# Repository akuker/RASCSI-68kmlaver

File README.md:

# RASCSI-68kmlaver
A scsi emulator based off of the work of http://www.geocities.jp/kugimoto0715/rascsi/index.html

# ATTENTION:
This repository is being archived. The current working version of the board has been moved to:
https://github.com/akuker/RASCSI/tree/master/hw/Dual_Connector_RaSCSI

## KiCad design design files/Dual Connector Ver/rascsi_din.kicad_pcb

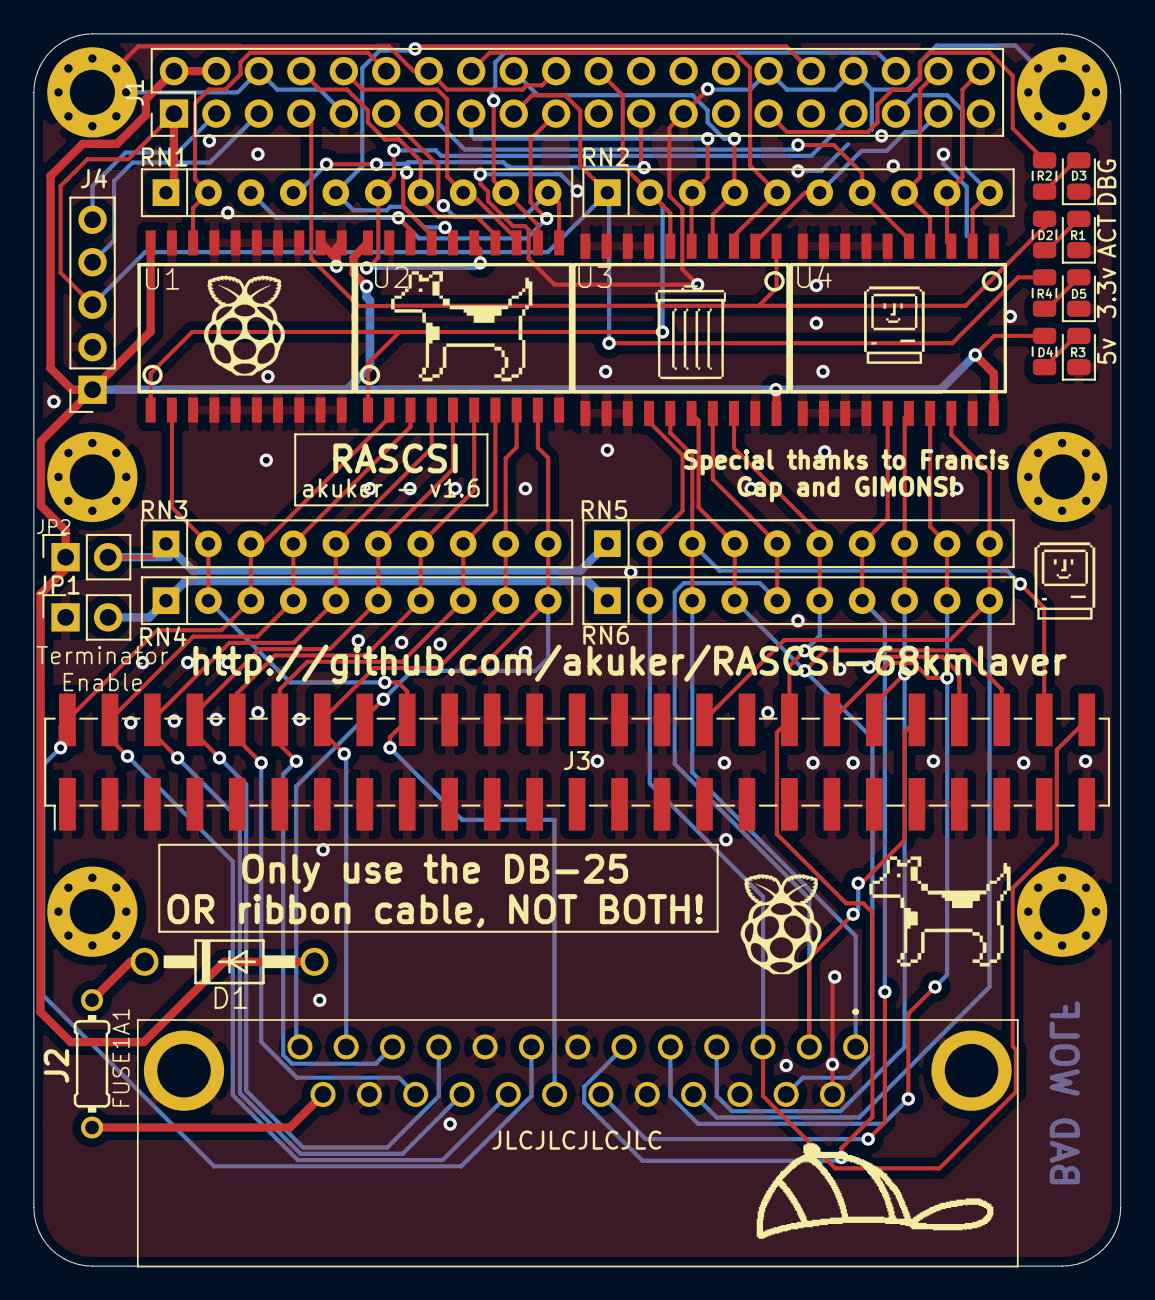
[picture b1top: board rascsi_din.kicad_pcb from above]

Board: 2 copper layers, 65.0 x 73.7 mm, 40 parts (0 on the bottom side), 51 nets.

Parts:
D1: 1N4004; DO41-10
D2, D3, D4, D5: LED_Small; LED_0805_2012Metric
FUSE1A1: R-US_0204_7; 0204_7
H1: Hole1; MountingHole_2.7mm_M2.5_Pad_Via
H2: Hole2; MountingHole_2.7mm_M2.5_Pad_Via
H3: Hole3; MountingHole_2.7mm_M2.5_Pad_Via
H4: Hole5; MountingHole_2.7mm_M2.5_Pad_Via
H5: Hole4; MountingHole_2.7mm_M2.5_Pad_Via
H6: Hole6; MountingHole_2.7mm_M2.5_Pad_Via
J1: Raspberry_Pi_2_3; PinHeader_2x20_P2.54mm_Vertical
J2: DLS3XS6AK44X
J3: Conn_02x25_Odd_Even; PinHeader_2x25_P2.54mm_Vertical_SMD
J4: I2C Pinout; PinSocket_1x05_P2.54mm_Vertical
JP1: Term_Enable_GND; PinSocket_1x02_P2.54mm_Vertical
JP2: Term_Enable_5v; PinSocket_1x02_P2.54mm_Vertical
L1: Mac; mac_happy_small
L2: Dogcow; dogcow
L3: Mac2; mac_happy_small
L4: Dogcow2; dogcow
L5, L7: Raspberry Pi; pi_logo
L6: Mac Trashcan; mac_trashcan
R1, R2, R4: 44; R_0805_2012Metric
R3: 112; R_0805_2012Metric
RN1, RN2: 10k; R_Array_SIP10
RN3, RN5: 220; R_Array_SIP10
RN4, RN6: 330; R_Array_SIP10
U1, U2, U3, U4: SN74LS641-1C; SOIC20S
U$1: LOGO

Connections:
+3V3: J1.1, J1.17, J4.3, R4.1, RN1.1, RN2.1
+5V: D1.A, J1.2, J1.4, J4.1, JP2.1, R3.1, U1.20, U2.20, U3.20, U4.20
C-ACK: J2.5, J3.38, RN5.9, RN6.9, U4.17
C-ATN: J2.17, J3.32, RN5.10, RN6.10, U4.18
C-BSY: J2.6, J3.36, RN5.6, RN6.6, U3.18
C-C_D: J2.15, J3.46, RN5.4, RN6.4, U3.16
C-D0: J2.8, J3.2, RN3.3, RN4.3, U2.2
C-D1: J2.21, J3.4, RN3.4, RN4.4, U2.3
C-D2: J2.22, J3.6, RN3.5, RN4.5, U2.4
C-D3: J2.10, J3.8, RN3.6, RN4.6, U2.5
C-D4: J2.23, J3.10, RN3.7, RN4.7, U2.6
C-D5: J2.11, J3.12, RN3.8, RN4.8, U2.7
C-D6: J2.12, J3.14, RN3.9, RN4.9, U2.8
C-D7: J2.13, J3.16, RN3.10, RN4.10, U2.9
C-DP: J2.20, J3.18, RN3.2, RN4.2, U1.2
C-I_O: J2.3, J3.50, RN5.2, RN6.2, U3.14
C-MSG: J2.2, J3.42, RN5.5, RN6.5, U3.17
C-REQ: J2.1, J3.48, RN5.3, RN6.3, U3.15
C-RST: J2.4, J3.40, RN5.8, RN6.8, U4.16
C-SEL: J2.19, J3.44, RN5.7, RN6.7, U4.15
DBG_LED: J1.29, R2.1
GND: D2.1, D3.1, D4.1, D5.1, H1.1, H2.1, H3.1, H4.1, H5.1, H6.1, J1.6, J1.9, J1.14, J1.20, J1.25, J1.30, J1.34, J1.39, J2.7, J2.9, J2.14, J2.16, J2.18, J2.24, J2.MH1, J2.MH2, J3.1, J3.3, J3.5, J3.7, J3.9, J3.11, J3.13, J3.15, J3.17, J3.19, J3.20, J3.21, J3.22, J3.23, J3.24, J3.27, J3.28, J3.29, J3.30, J3.31, J3.33, J3.35, J3.37, J3.39, J3.41, J3.43, J3.45, J3.47, J3.49, J4.2, JP1.1, U1.3, U1.4, U1.5, U1.6, U1.7, U1.8, U1.9, U1.10, U1.11, U1.12, U1.13, U1.14, U1.15, U1.16, U1.17, U1.19, U2.10, U2.19, U3.7, U3.8, U3.9, U3.10, U3.11, U3.12, U3.13, U3.19, U4.1, U4.6, U4.7, U4.8, U4.9, U4.10, U4.11, U4.12, U4.13, U4.14, U4.19
unnamed: D1.C, FUSE1A1.2
unnamed: D2.2, R1.2
unnamed: D3.2, R2.2
unnamed: D4.2, R3.2
unnamed: D5.2, R4.2
unnamed: JP1.2, RN4.1, RN6.1
unnamed: JP2.2, RN3.1, RN5.1
PI-ACK: J1.40, RN2.9, U4.3
PI-ACT: J1.7, R1.1, U3.1
PI-ATN: J1.35, RN2.10, U4.2
PI-BSY: J1.37, RN2.6, U3.2
PI-C_D: J1.18, RN2.4, U3.4
PI-D0: J1.19, RN1.3, U2.18
PI-D1: J1.23, RN1.4, U2.17
PI-D2: J1.32, RN1.5, U2.16
PI-D3: J1.33, RN1.6, U2.15
PI-D4: J1.8, RN1.7, U2.14
PI-D5: J1.10, RN1.8, U2.13
PI-D6: J1.36, RN1.9, U2.12
PI-D7: J1.11, RN1.10, U2.11
PI-DP: J1.12, RN1.2, U1.18
PI-I_O: J1.22, RN2.2, U1.1, U2.1, U3.6
PI-MSG: J1.16, RN2.5, U3.3
PI-REQ: J1.15, RN2.3, U3.5
PI-RST: J1.38, RN2.8, U4.4
PI-SEL: J1.13, RN2.7, U4.5
PI_SCL: J1.5, J4.4
PI_SDA: J1.3, J4.5
TERMPOW: FUSE1A1.1, J2.25

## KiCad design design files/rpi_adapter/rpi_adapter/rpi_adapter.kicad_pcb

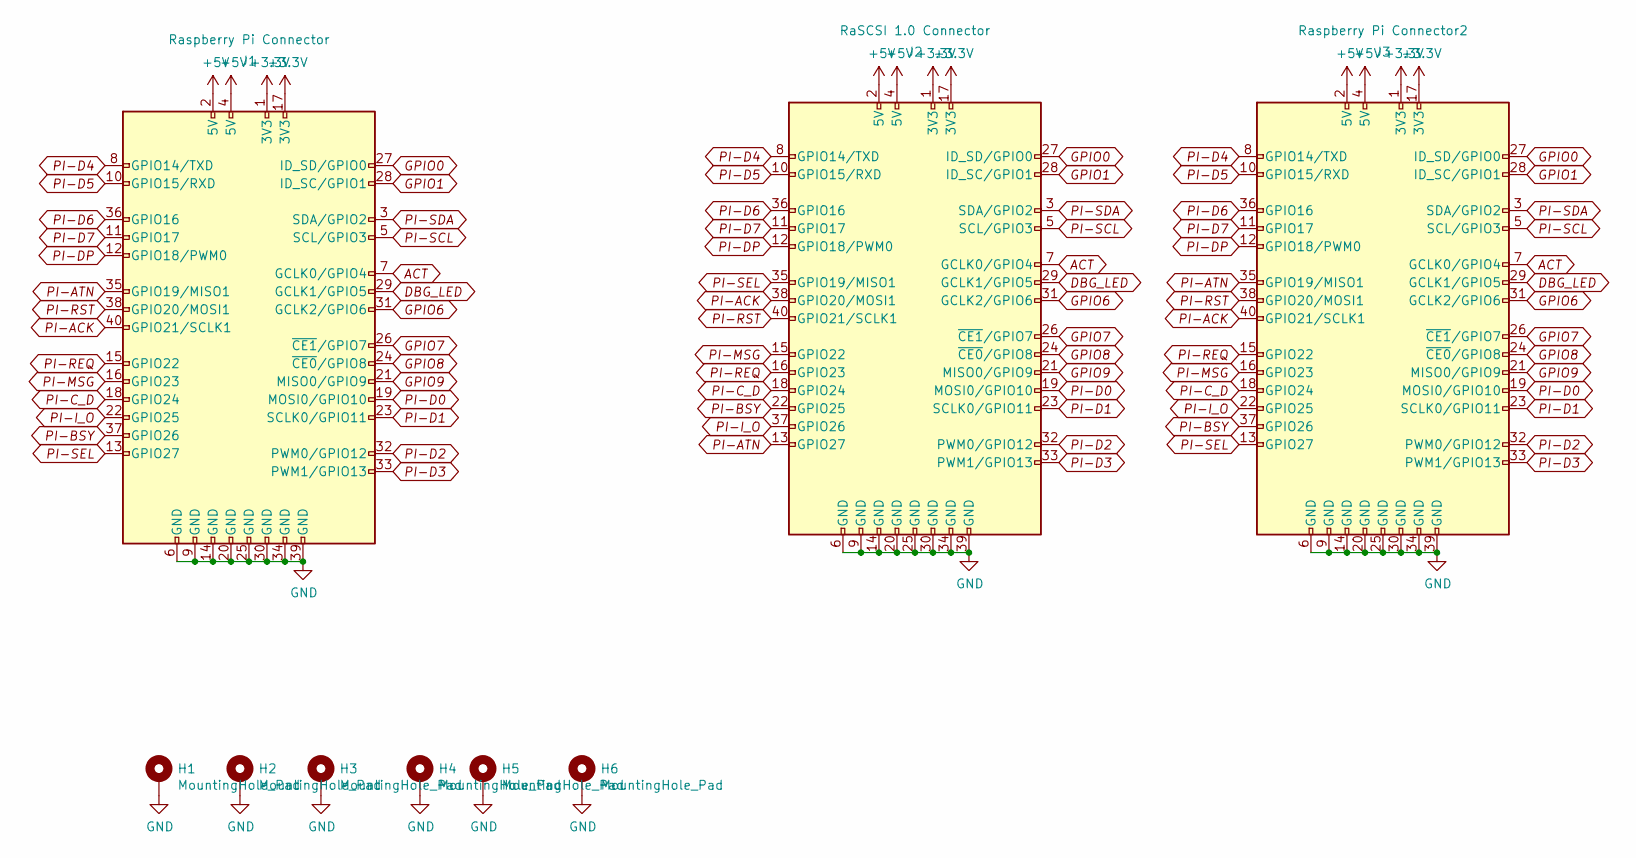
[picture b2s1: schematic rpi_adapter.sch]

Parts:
H1, H2, H3, H4, H5, H6: MountingHole_Pad; MountingHole_2.7mm_M2.5_Pad_Via
J1: Raspberry Pi Connector; PinHeader_2x20_P2.54mm_Vertical
J2: RaSCSI 1.0 Connector; PinHeader_2x20_P2.54mm_Vertical
J3: Raspberry Pi Connector2; PinHeader_2x20_P2.54mm_Vertical

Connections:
+3V3: J1.1 (3V3), J1.17 (3V3), J2.1 (3V3), J2.17 (3V3), J3.1 (3V3), J3.17 (3V3)
+5V: J1.2 (5V), J1.4 (5V), J2.2 (5V), J2.4 (5V), J3.2 (5V), J3.4 (5V)
ACT: J1.7 (GCLK0/GPIO4), J2.7 (GCLK0/GPIO4), J3.7 (GCLK0/GPIO4)
DBG_LED: J1.29 (GCLK1/GPIO5), J2.29 (GCLK1/GPIO5), J3.29 (GCLK1/GPIO5)
GND: H1.1, H2.1, H3.1, H4.1, H5.1, H6.1, J1.6 (GND), J1.9 (GND), J1.14 (GND), J1.20 (GND), J1.25 (GND), J1.30 (GND), J1.34 (GND), J1.39 (GND), J2.6 (GND), J2.9 (GND), J2.14 (GND), J2.20 (GND), J2.25 (GND), J2.30 (GND), J2.34 (GND), J2.39 (GND), J3.6 (GND), J3.9 (GND), J3.14 (GND), J3.20 (GND), J3.25 (GND), J3.30 (GND), J3.34 (GND), J3.39 (GND)
GPIO0: J1.27 (ID_SD/GPIO0), J2.27 (ID_SD/GPIO0), J3.27 (ID_SD/GPIO0)
GPIO1: J1.28 (ID_SC/GPIO1), J2.28 (ID_SC/GPIO1), J3.28 (ID_SC/GPIO1)
GPIO6: J1.31 (GCLK2/GPIO6), J2.31 (GCLK2/GPIO6), J3.31 (GCLK2/GPIO6)
GPIO7: J1.26 (~CE1~/GPIO7), J2.26 (~CE1~/GPIO7), J3.26 (~CE1~/GPIO7)
GPIO8: J1.24 (~CE0~/GPIO8), J2.24 (~CE0~/GPIO8), J3.24 (~CE0~/GPIO8)
GPIO9: J1.21 (MISO0/GPIO9), J2.21 (MISO0/GPIO9), J3.21 (MISO0/GPIO9)
PI-ACK: J1.40 (GPIO21/SCLK1), J2.38 (GPIO20/MOSI1), J3.40 (GPIO21/SCLK1)
PI-ATN: J1.35 (GPIO19/MISO1), J2.13 (GPIO27), J3.35 (GPIO19/MISO1)
PI-BSY: J1.37 (GPIO26), J2.22 (GPIO25), J3.37 (GPIO26)
PI-C_D: J1.18 (GPIO24), J2.18 (GPIO24), J3.18 (GPIO24)
PI-D0: J1.19 (MOSI0/GPIO10), J2.19 (MOSI0/GPIO10), J3.19 (MOSI0/GPIO10)
PI-D1: J1.23 (SCLK0/GPIO11), J2.23 (SCLK0/GPIO11), J3.23 (SCLK0/GPIO11)
PI-D2: J1.32 (PWM0/GPIO12), J2.32 (PWM0/GPIO12), J3.32 (PWM0/GPIO12)
PI-D3: J1.33 (PWM1/GPIO13), J2.33 (PWM1/GPIO13), J3.33 (PWM1/GPIO13)
PI-D4: J1.8 (GPIO14/TXD), J2.8 (GPIO14/TXD), J3.8 (GPIO14/TXD)
PI-D5: J1.10 (GPIO15/RXD), J2.10 (GPIO15/RXD), J3.10 (GPIO15/RXD)
PI-D6: J1.36 (GPIO16), J2.36 (GPIO16), J3.36 (GPIO16)
PI-D7: J1.11 (GPIO17), J2.11 (GPIO17), J3.11 (GPIO17)
PI-DP: J1.12 (GPIO18/PWM0), J2.12 (GPIO18/PWM0), J3.12 (GPIO18/PWM0)
PI-I_O: J1.22 (GPIO25), J2.37 (GPIO26), J3.22 (GPIO25)
PI-MSG: J1.16 (GPIO23), J2.15 (GPIO22), J3.16 (GPIO23)
PI-REQ: J1.15 (GPIO22), J2.16 (GPIO23), J3.15 (GPIO22)
PI-RST: J1.38 (GPIO20/MOSI1), J2.40 (GPIO21/SCLK1), J3.38 (GPIO20/MOSI1)
PI-SCL: J1.5 (SCL/GPIO3), J2.5 (SCL/GPIO3), J3.5 (SCL/GPIO3)
PI-SDA: J1.3 (SDA/GPIO2), J2.3 (SDA/GPIO2), J3.3 (SDA/GPIO2)
PI-SEL: J1.13 (GPIO27), J2.35 (GPIO19/MISO1), J3.13 (GPIO27)

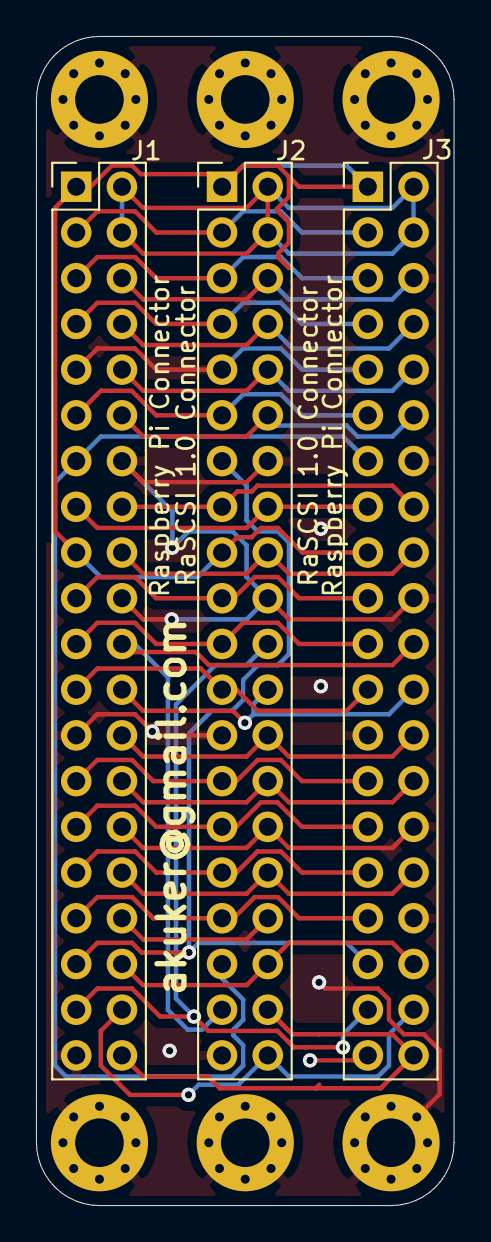
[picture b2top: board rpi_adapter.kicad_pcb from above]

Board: 2 copper layers, 23.2 x 65.0 mm, 9 parts (0 on the bottom side), 31 nets.

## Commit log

2020-06-26 Moved 50-pin Ribbon version of the board into a directory Added a dual-connector version of the board. (New board is in KiCad, not Eagle)
2020-06-26 Add silk screen art and clean up labels
2020-06-27 Cleanup and created BOM and Gerber files
2020-06-28 Created adapter to correct pin layout on version 1.0. Also created version 1.5 which corrects the connections
2020-06-28 Corrected pinout to match original RaSCSI design.
2020-07-08 Restored the correct version of the schematic & added notes to fix the PI-ACT signal. Also adding the gerber files.
2020-07-08 Remove extraneous files
2020-07-08 Corrected ACT signal line
